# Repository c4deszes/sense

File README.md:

# Environment sensor

> This project implements an environment sensor, including PCB, enclosure and
software.

---

## Features

+ WiFi connection, configuration in AP mode
+ Publishes messages over MQTT
+ Measures several values, including:
  + Temperature
  + Humidity
  + Pressure
  + Dust concentration
  + Wind speed
  + Light level

## Help

### Documentation

The project uses AsciiDoctor as it's primary documentation format and Markdown
in a few places, such as this README.

[AsciiDoctor reference](https://docs.asciidoctor.org/asciidoc/latest/)

[AsciiDoctor Gradle plugin](https://asciidoctor.github.io/asciidoctor-gradle-plugin/development-3.x/user-guide)

### Traceability

Project is setup to have traceability from requirements to implementation and
verification but hasn't decided on a tool yet.

## License

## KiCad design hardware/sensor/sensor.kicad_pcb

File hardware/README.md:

# Sensor Hardware

## Requirements

[List of hardware requirements](./docs/requirements)

## Design

[Hardware design overview](./docs/design/hardware.adoc)

## Development process

Development process according to [Hardware SPICE](https://www.intacs.info/images/uploads/intacs_HW_Engineering_PRM_PAM_v20.pdf).

---

## Development tools

| Tool | Version | Purpose |
|--|--|--|
| KiCAD | 5.1+ | Schematic design, PCB layout |
| Python | 3.8+ | *Optional*, used for scripted workflow |

---

## Continuous Integration

GitHub Actions is used for automatically testing some aspects of the design on
each change.

[KiBot](https://github.com/INTI-CMNB/kibot)

[KiCAD Export actions](https://github.com/nerdyscout/kicad-exports)

---

## Helpful links

[Hardware Software Interface](https://nqa2.iscn.com/images/PdfFiles/experience-aspice-safety-integrated.pdf)

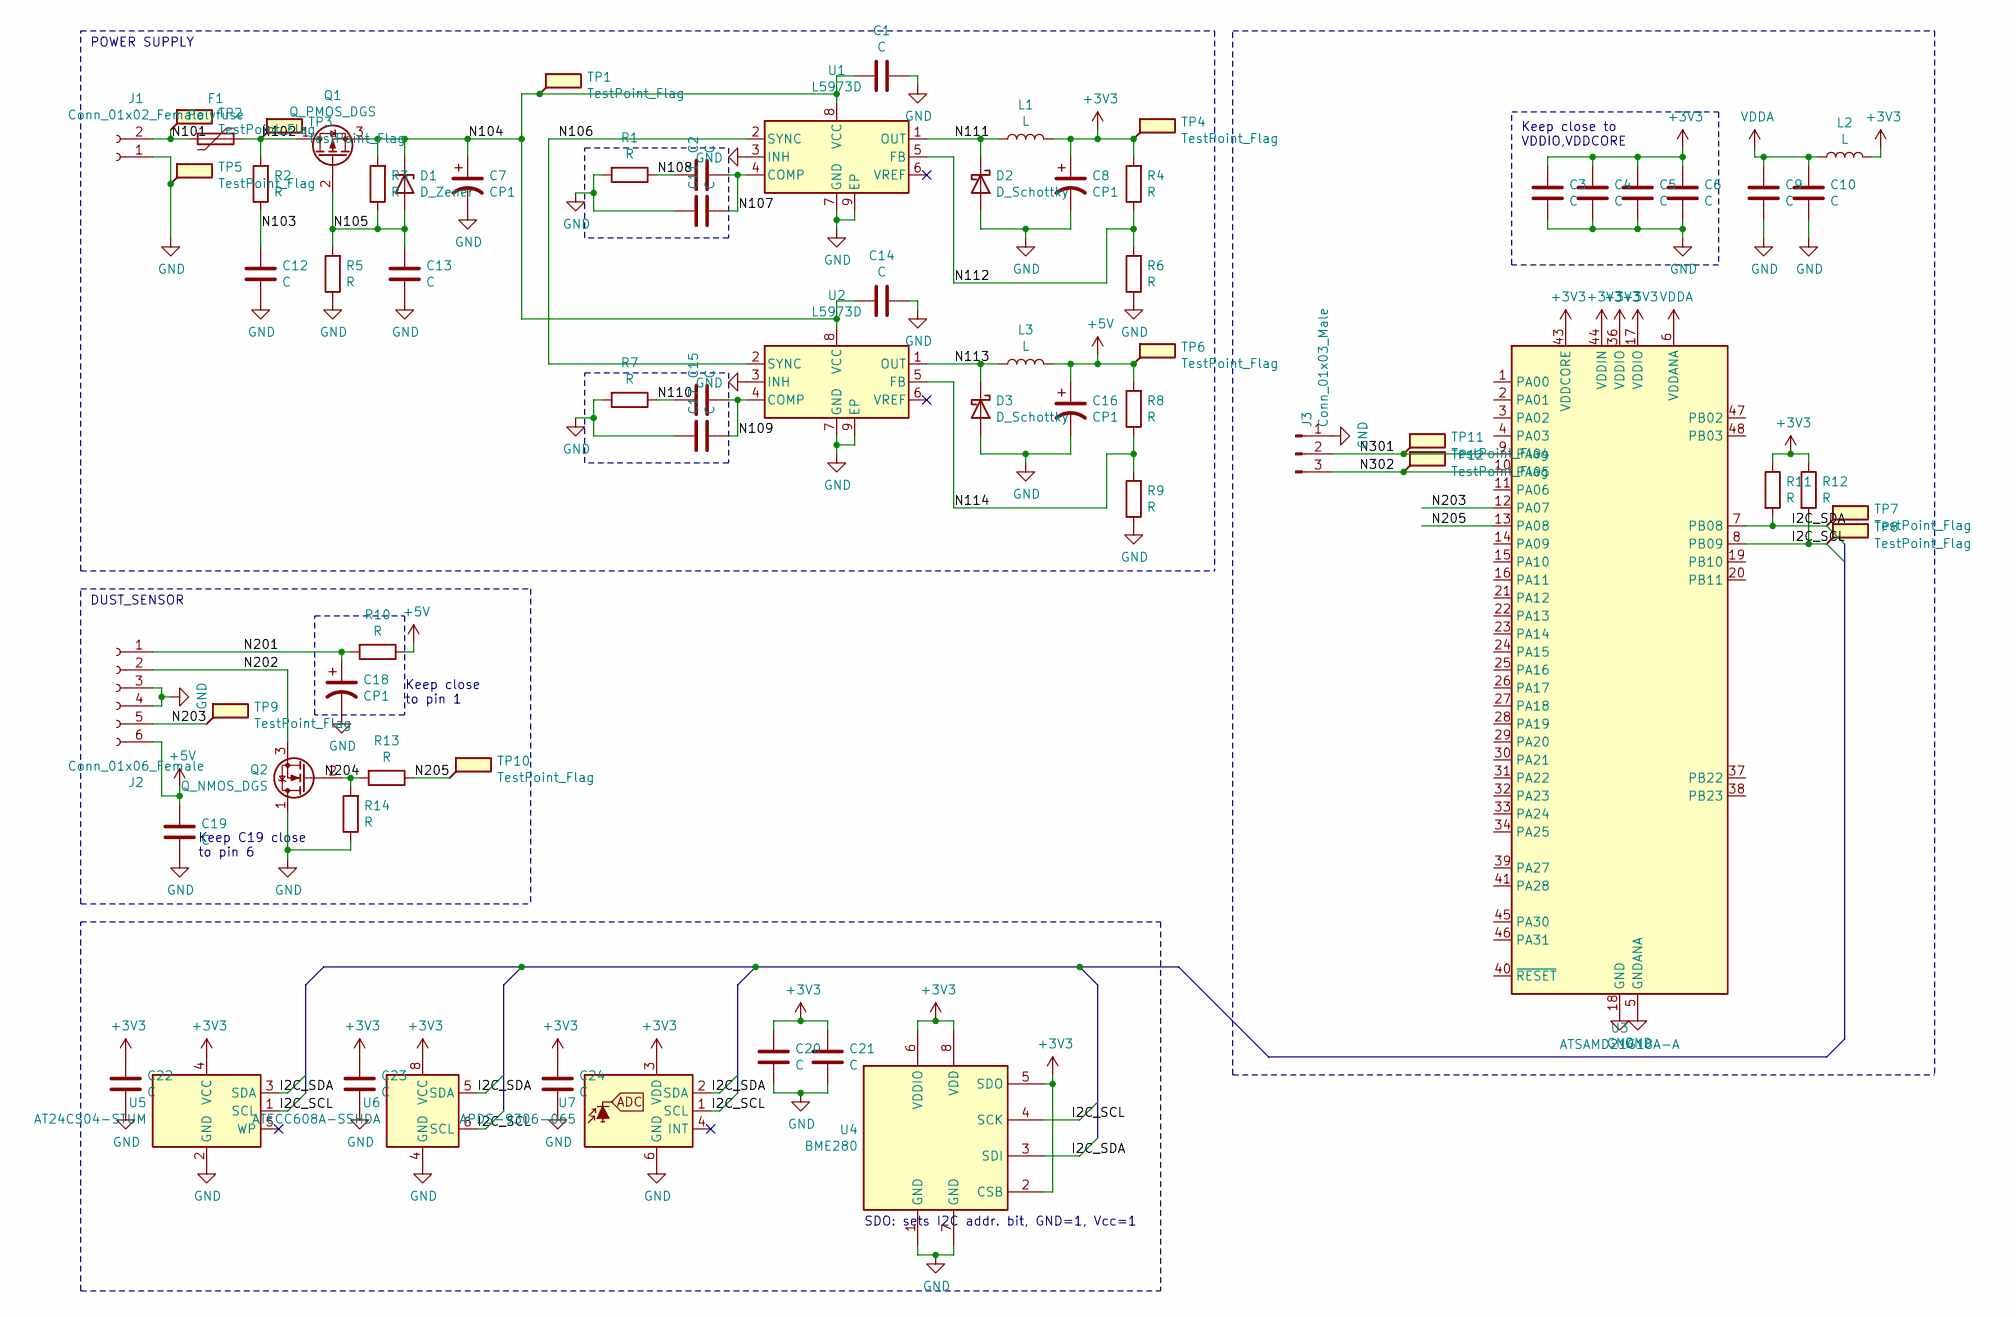
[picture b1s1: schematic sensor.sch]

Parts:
C1, C2, C3, C4, C5, C6, C9, C10, C11, C12, C13, C14, C15, C17, C19, C20, C21, C22, C23, C24: C; C_0603_1608Metric
C7, C8, C16, C18: CP1; CP_Elec_6.3x7.7
D1: D_Zener; D_SOD-110
D2, D3: D_Schottky; D_SMB_Handsoldering
F1: Polyfuse; Fuse_1812_4532Metric
J1: Conn_01x02_Female; JST_EH_S2B-EH_1x02_P2.50mm_Horizontal
J2: Conn_01x06_Female; PinHeader_1x06_P2.54mm_Vertical
J3: Conn_01x03_Male; PinHeader_1x03_P2.54mm_Vertical
L1, L3: L; L_Bourns-SRN4018
L2: L; L_0805_2012Metric
Q1: Q_PMOS_DGS; TO-252-2
Q2: Q_NMOS_DGS; SOT-23
R1, R2, R3, R4, R5, R6, R7, R8, R9, R10, R11, R12, R13, R14: R; R_0603_1608Metric
TP1, TP2, TP3, TP4, TP5, TP6, TP7, TP8, TP9, TP10, TP11, TP12: TestPoint_Flag; TestPoint_Pad_D1.5mm
U1, U2: L5973D; HSOP-8-1EP_3.9x4.9mm_P1.27mm_EP2.41x3.1mm_ThermalVias
U3: ATSAMD21G18A-A; TQFP-48_7x7mm_P0.5mm
U4: BME280; Bosch_LGA-8_2.5x2.5mm_P0.65mm_ClockwisePinNumbering
U5: AT24CS04-STUM; SOT-23-5
U6: ATECC608A-SSHDA; SOIC-8_3.9x4.9mm_P1.27mm
U7: APDS-9306-065; Broadcom_DFN-6_2x2mm_P0.65mm

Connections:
+3V3: C3.1, C4.1, C5.1, C6.1, C8.1, C20.1, C21.1, C22.1, C23.1, C24.1, L1.2, L2.2, R4.2, R11.1, R12.1, TP4.1, U3.17 (VDDIO), U3.36 (VDDIO), U3.43 (VDDCORE), U3.44 (VDDIN), U4.2 (CSB), U4.5 (SDO), U4.6 (VDDIO), U4.8 (VDD), U5.4 (VCC), U6.8 (VCC), U7.3 (VDD)
+5V: C16.1, C19.1, J2.6, L3.2, R8.2, R10.1, TP6.1
/I2C_SCL: R12.2, TP8.1, U3.8 (PB09), U4.4 (SCK), U5.1 (SCL), U6.6 (SCL), U7.1 (SCL)
/I2C_SDA: R11.2, TP7.1, U3.7 (PB08), U4.3 (SDI), U5.3 (SDA), U6.5 (SDA), U7.2 (SDA)
/N101: F1.2, J1.2, TP2.1
/N102: F1.1, Q1.1 (D), R2.2, TP3.1
/N103: C12.1, R2.1
/N104: C1.1, C7.1, C14.1, D1.1 (K), Q1.3 (S), R3.2, TP1.1, U1.8 (VCC), U2.8 (VCC)
/N105: C13.1, D1.2 (A), Q1.2 (G), R3.1, R5.2
/N106: U1.2 (SYNC), U2.2 (SYNC)
/N107: C2.2, C11.2, U1.4 (COMP)
/N108: C2.1, R1.1
/N109: C15.2, C17.2, U2.4 (COMP)
/N110: C15.1, R7.1
/N111: D2.1 (K), L1.1, U1.1 (OUT)
/N112: R4.1, R6.2, U1.5 (FB)
/N113: D3.1 (K), L3.1, U2.1 (OUT)
/N114: R8.1, R9.2, U2.5 (FB)
/N201: C18.1, J2.1, R10.2
/N202: J2.2, Q2.3 (S)
/N203: J2.5, TP9.1, U3.12 (PA07)
/N205: R13.1, TP10.1, U3.13 (PA08)
/N301: J3.2, TP11.1, U3.9 (PA04)
/N302: J3.3, TP12.1, U3.10 (PA05)
GND: C1.2, C3.2, C4.2, C5.2, C6.2, C7.2, C8.2, C9.2, C10.2, C11.1, C12.2, C13.2, C14.2, C16.2, C17.1, C18.2, C19.2, C20.2, C21.2, C22.2, C23.2, C24.2, D2.2 (A), D3.2 (A), J1.1, J2.3, J2.4, J3.1, Q2.1 (D), R1.2, R5.1, R6.1, R7.2, R9.1, R14.1, TP5.1, U1.3 (INH), U1.7 (GND), U1.9 (EP), U2.3 (INH), U2.7 (GND), U2.9 (EP), U3.5 (GNDANA), U3.18 (GND), U3.35 (GND), U3.42 (GND), U4.1 (GND), U4.7 (GND), U5.2 (GND), U6.4 (GND), U7.6 (GND)
unnamed: Q2.2 (G), R13.2, R14.2
VDDA: C9.1, C10.1, L2.1, U3.6 (VDDANA)

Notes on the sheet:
SDO: sets I2C addr. bit, GND=1, Vcc=1
DUST_SENSOR
POWER SUPPLY
Keep close to pin 1
Keep C19 close to pin 6
Keep close to VDDIO,VDDCORE

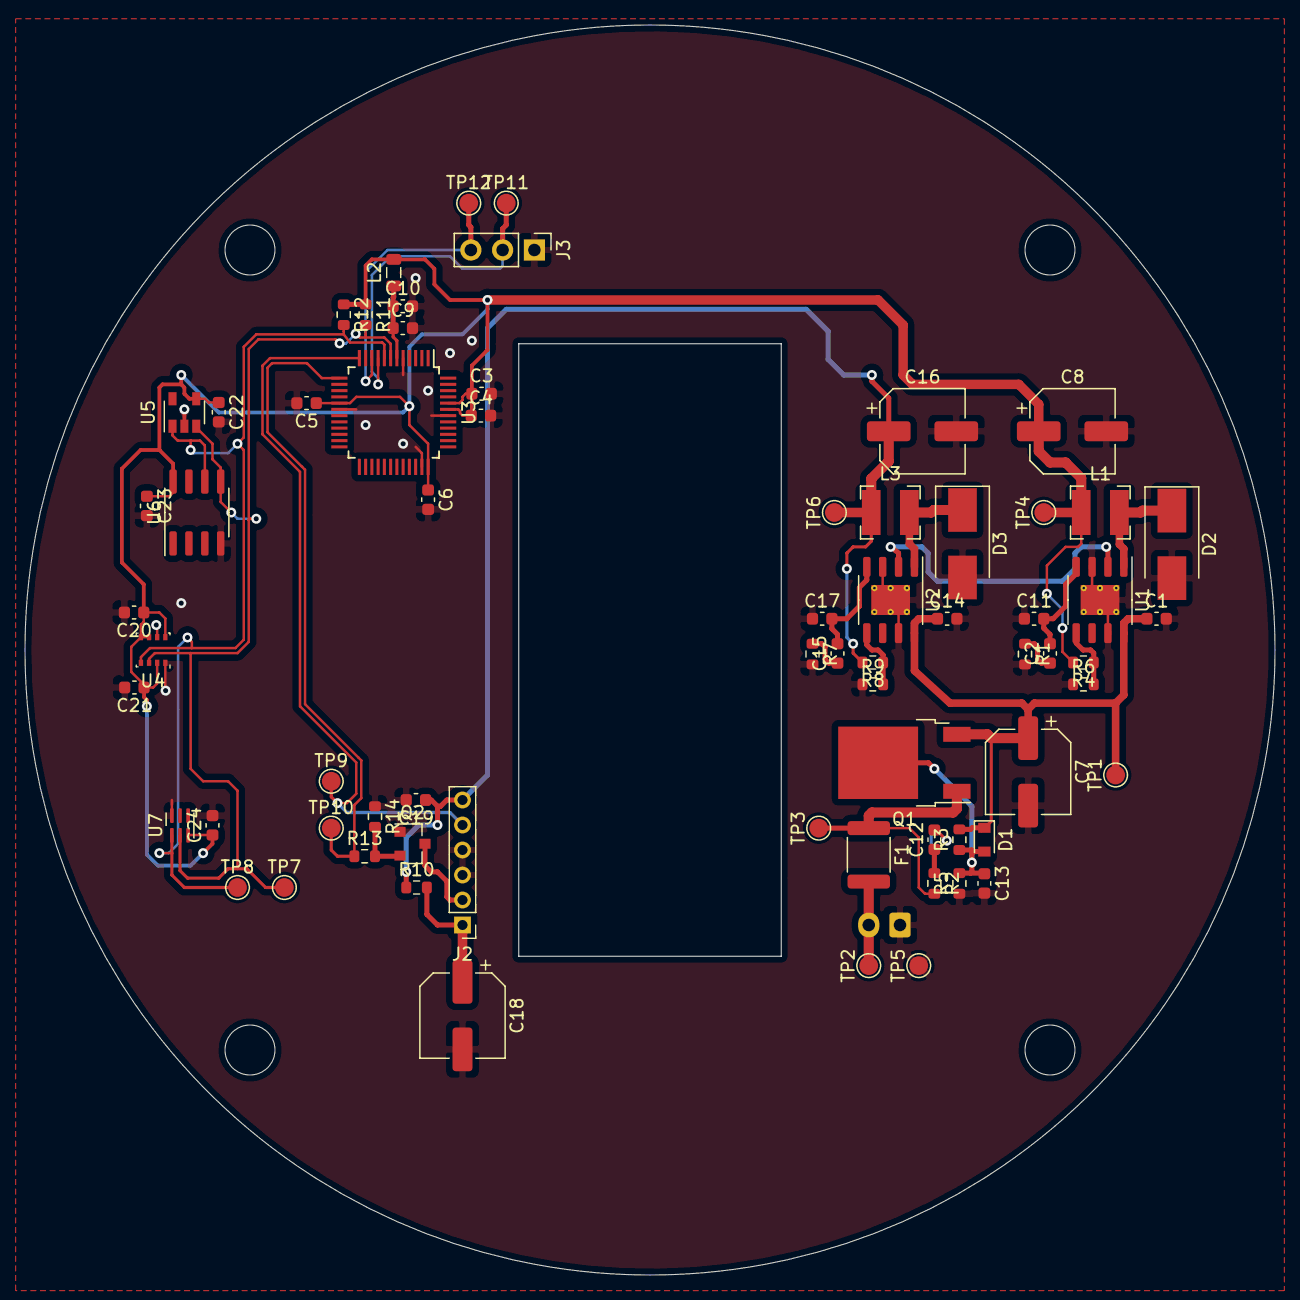
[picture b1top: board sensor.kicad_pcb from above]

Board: 2 copper layers, 100.0 x 100.0 mm, 69 parts (1 on the bottom side), 27 nets.

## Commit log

2021-01-30 Initial commit
    Adds system requirements
    Adds system parameters
    Adds README and LICENSE
2021-02-02 Adds initial system architecture
    New WiFi requirements: module error and configuration error
    Adds System overview document
    Fixed links in system documentation
    Adds Gradle buildscripts for Asciidoc rendering
2021-02-02 Adds PR labeler
2021-02-02 Adds initial system architecture (#1)
    New WiFi requirements: module error and configuration error
    Adds System overview document
    Fixed links in system documentation
    Adds Gradle buildscripts for Asciidoc rendering
2021-02-04 Adds initial software requirements
    Adds asciidoc generator task to software project
2021-02-07 Finalizes initial software requirements
    Fixes links in sw. comm. requirements
    Doc builds run from root directory
    Updates links in sys. requirements
2021-02-07 Adds initial software requirements (#2)
    * Adds initial software requirements
    Adds asciidoc generator task to software project
    Doc builds run from root directory
    Fixes links in sw. comm. requirements
    Updates links in sys. requirements
2021-02-12 Adds initial software architecture
    Adds asciidoctor-diagram support for software and system
    Adds software arch. design alternatives
2021-02-15 Adds individual software element designs
    Adds links to elements in software architecture
2021-02-15 Initial software architecture (#3)
    Adds initial software architecture
    Adds software arch. design alternatives
    Adds individual software element designs
    Adds asciidoctor-diagram support for software and system
2021-02-17 Adds Gradle wrapper to the project
2021-02-17 Adds initial hardware requirements
    Adds hardware subproject
    Adds hardware parameters
    Fixes newline at the end of csv files causing errors in previews
2021-02-17 Adds hardware domain to PR labeler
2021-02-18 Adds initial hardware requirements (#4)
    Adds hardware subproject
    Adds hardware parameters
    Adds hardware domain to PR labeler
    Fixes newline at the end of csv files causing errors in previews
2021-02-18 Adds documentation help section to root README
2021-02-19 Adds initial design with parts suggestions
2021-02-19 Adds hw design automatic label
2021-02-19 Initial hardware design (#5)
    Adds initial design with parts suggestions
    Adds hw design automatic label
2021-03-14 Adds V&V documents for SYS/SW/HW domains
    Adds SYS Test environment and test process documents
    Adds SW Test environment and test process documents
    Adds HW Test environment and test process documents
2021-03-14 Adds SYS Readme
2021-03-14 Verification & Validation strategy (#6)
    * Adds V&V documents for SYS/SW/HW domains
    Adds SYS Test environment and test process documents
    Adds SW Test environment and test process documents
    Adds HW Test environment and test process documents
    Adds SYS Readme
2021-03-15 Initial hardware schematic and layout
    Adds hardware workflow with Gerber and BOM export
    Adds hardware parameters
    Adds HSI configuration
    Adds KiCad schematic and layout
2021-03-15 Removes local library
2021-03-15 Fixes kibot steps missing -b argument
2021-03-15 Modifies hardware workflow
    Merges Gerber and BOM jobs
    Adds shematic and layout export steps
2021-03-16 Adds ERC & DRC verification step
2021-03-16 Fixes DRC & ERC configuration
    Adds step to upload ERC & DRC report
2021-03-16 Separates ERC & DRC steps
    DRC now depends on ERC
    Manufacturing output is now only generated if DRC passes
2021-03-17 Initial layout is complete
    Removes mounting points as they're present in the DXF
2021-03-18 Fixes power input clearance
2021-03-19 Adds stages to generate 3D model and 2D render
2021-06-22 Initial hardware schematic and layout (#7)
    Adds KiCad schematic and layout
    Adds hardware parameters and HSI configuration
    Adds hardware workflow with Gerber, BOM, Layout and schematic export
2021-07-04 Adds PR and issue templates

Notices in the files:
README.md:
License:
[License: MIT](https://opensource.org/licenses/MIT)
License: MIT
